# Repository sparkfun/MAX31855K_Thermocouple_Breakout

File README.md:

MAX31855K Thermocouple Breakout
========================================

[*SEN-13266*](https://www.sparkfun.com/products/13266)

The [MAX31855K](http://datasheets.maximintegrated.com/en/ds/MAX31855.pdf) IC takes a standard k-type thermocouple in one end, digitizes the temperature measured and sends that data out the other end via [SPI](http://en.wikipedia.org/wiki/Serial_Peripheral_Interface_Bus).

This part was created in Eagle v7.2.0.

Repository Contents
-------------------

* **/Hardware** - All Eagle design files (.brd, .sch)
* **/Libraries** - All Arduino libraries and board examples
* **/Production** - Test bed files and production panel files
* **LICENSE.md** - The license this library is distributed under.
* **README.md** - This file!

Documentation
--------------

* **[Installing an Arduino Library Guide](https://learn.sparkfun.com/tutorials/installing-an-arduino-library)** - Basic information on how to install an Arduino library.
* **[Hookup Guide](https://learn.sparkfun.com/tutorials/max31855k-thermocouple-breakout-hookup-guide)** - Basic hookup guide for the MAX31855K Thermocouple Breakout.

Product Versions
----------------
* [*SEN-13266*](https://www.sparkfun.com/products/13266) - K-type thermocouple digitizer breakout board

Version History
---------------
* [v1.0](https://www.sparkfun.com/products/13266) MAX31855K Thermocouple Breakout

License Information
-------------------

This product is _**open source**_!

Please review the LICENSE.md file for license information.

If you have any questions or concerns on licensing, please contact techsupport@sparkfun.com.

Distributed as-is; no warranty is given.

- Your friends at SparkFun.

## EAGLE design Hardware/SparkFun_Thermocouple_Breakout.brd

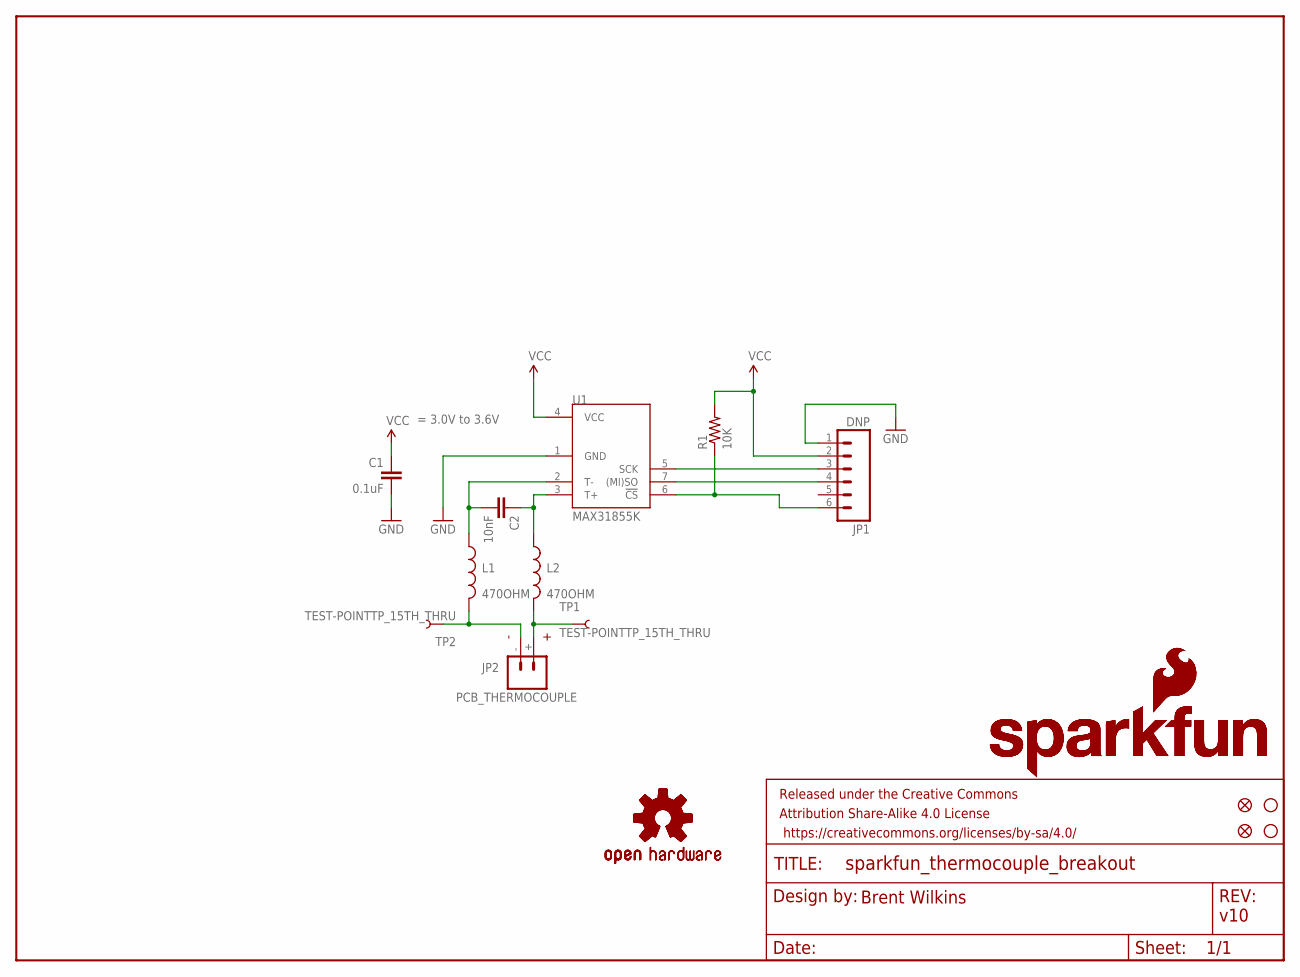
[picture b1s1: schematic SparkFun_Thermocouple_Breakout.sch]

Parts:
C1: 0.1uF; 0603-CAP
C2: 10nF; 0603-CAP
FID1, FID2: FIDUCIAL1X2; FIDUCIAL-1X2
FRAME1: >VERSION; CREATIVE_COMMONS
JP1: DNP; 1X06
JP2: PCB_THERMOCOUPLE; PCC-SMP
L1, L2: 470OHM; 0603
LOGO1, LOGO4: OSHW-LOGOS; OSHW-LOGO-S
LOGO2, LOGO3: SFE_LOGO_NAME_FLAME.1_INCH; SFE_LOGO_NAME_FLAME_.1
R1: 10K; 0603-RES
STANDOFF1, STANDOFF4: STAND-OFF
TP1, TP2: TEST-POINTTP_15TH_THRU; TP_15TH
U1: MAX31855K; SOIC8

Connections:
GND: C1.2, JP1.1, U1.1 (GND)
unnamed: JP1.3, U1.5 (SCK)
unnamed: JP1.4, U1.7 ((MI)SO)
unnamed: C2.2, L1.1, U1.2 (T-)
unnamed: JP2.+, L2.2, TP1.P$1
unnamed: JP2.-, L1.2, TP2.P$1
unnamed: C2.1, L2.1, U1.3 (T+)
unnamed: JP1.6, R1.1, U1.6 (!CS)
VCC: C1.1, JP1.2, R1.2, U1.4 (VCC)

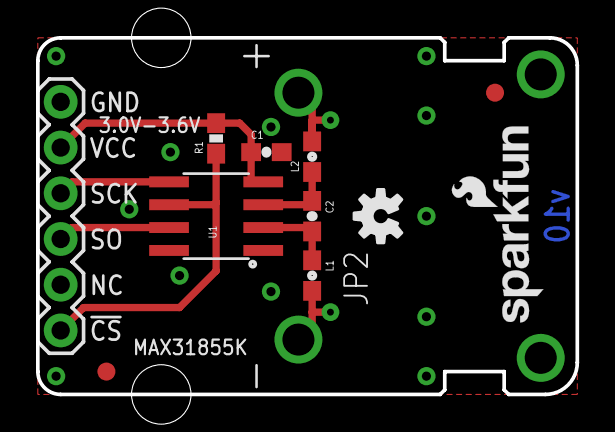
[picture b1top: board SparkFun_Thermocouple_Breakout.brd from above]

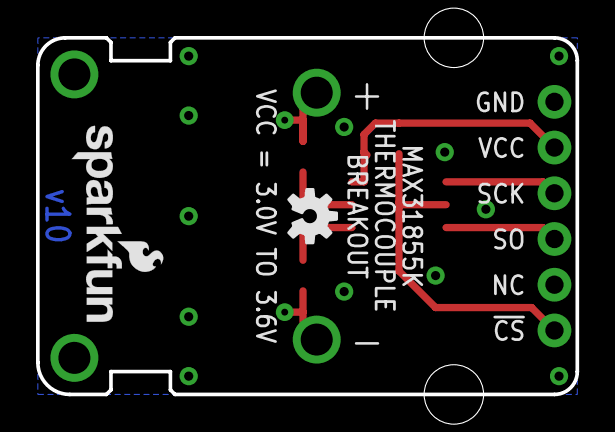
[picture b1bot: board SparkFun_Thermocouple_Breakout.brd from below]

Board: 2 copper layers, 30.0 x 19.8 mm, 19 parts (2 on the bottom side), 9 nets.

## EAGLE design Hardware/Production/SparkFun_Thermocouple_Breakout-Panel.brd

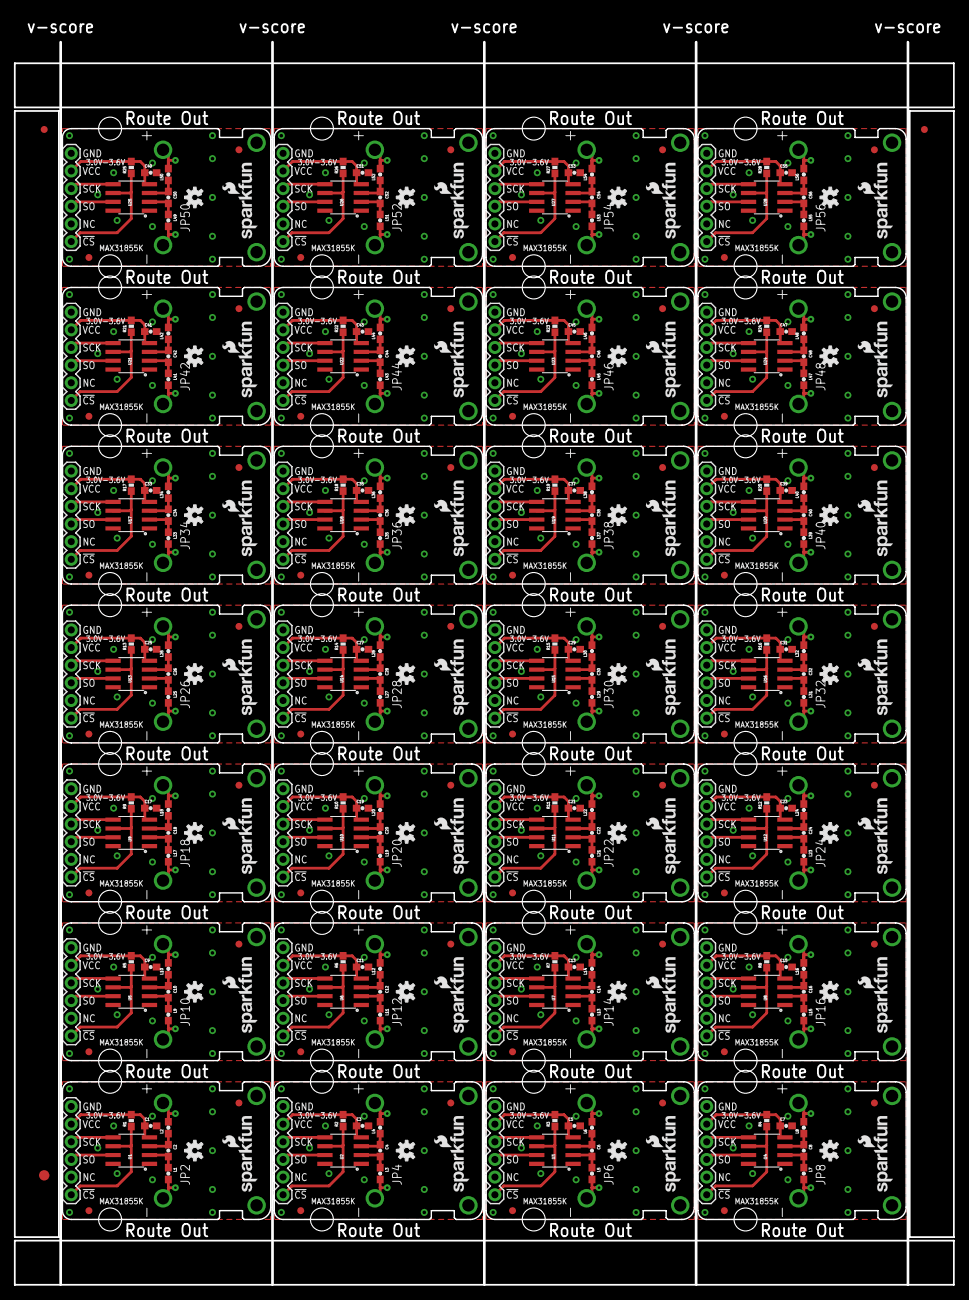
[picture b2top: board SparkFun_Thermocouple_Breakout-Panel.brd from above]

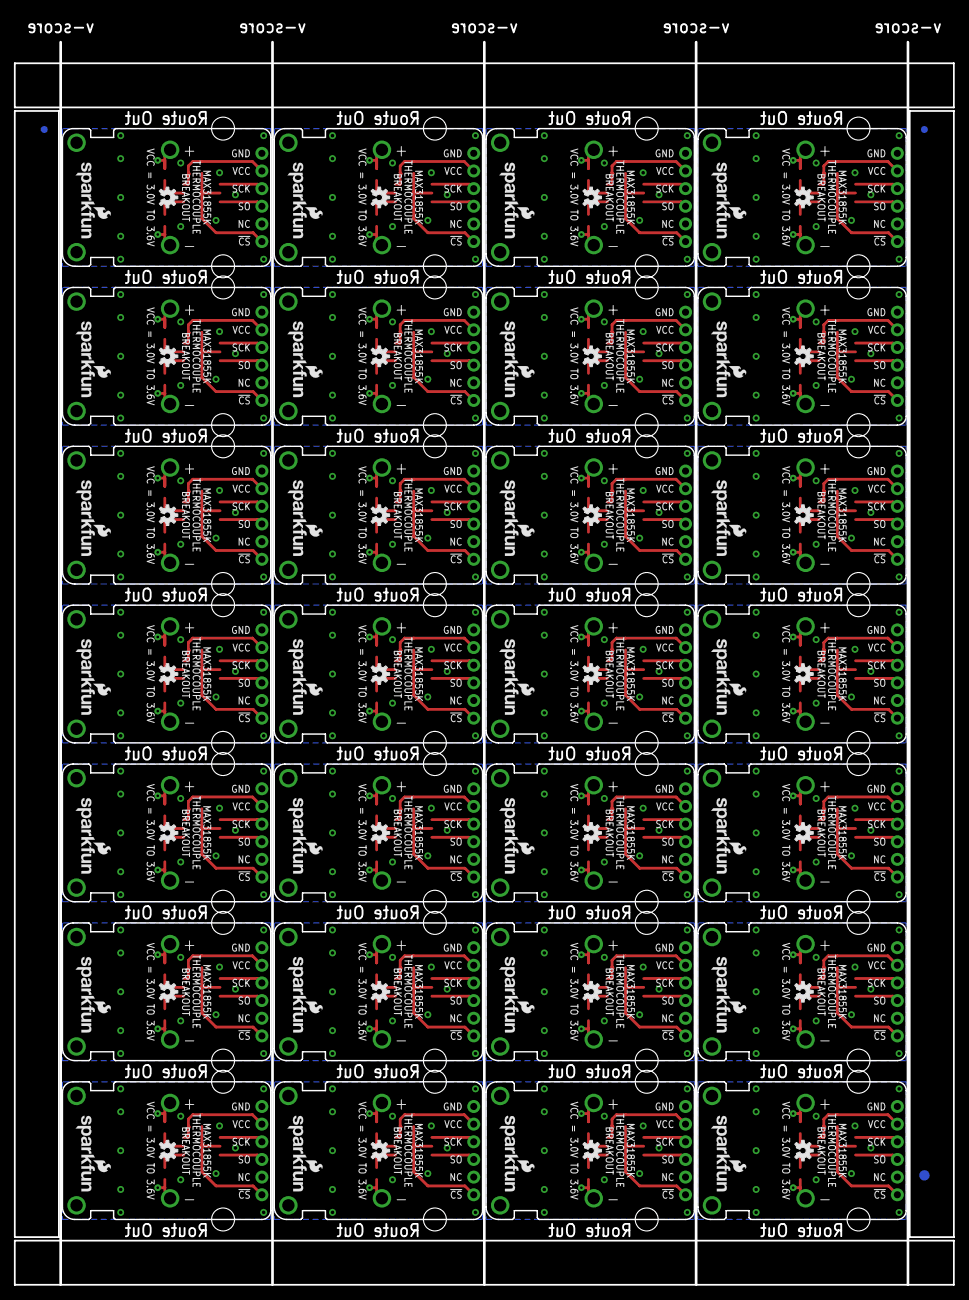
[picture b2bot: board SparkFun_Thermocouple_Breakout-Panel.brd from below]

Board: 2 copper layers, 135.0 x 182.7 mm, 510 parts (59 on the bottom side), 252 nets.

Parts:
C1, C3, C5, C7, C9, C11, C13, C15, C17, C19, C21, C23, C25, C27, C29, C31, C33, C35, C37, C39, C41, C43, C45, C47, C49, C51, C53, C55: 0.1uF; 0603-CAP
C2, C4, C6, C8, C10, C12, C14, C16, C18, C20, C22, C24, C26, C28, C30, C32, C34, C36, C38, C40, C42, C44, C46, C48, C50, C52, C54, C56: 10nF; 0603-CAP
E$1, E$2, E$3, E$4: FIDUCIAL-1X2
E$5, E$6: FIDUCIAL-1.5X3
FID1, FID2, FID3, FID4, FID5, FID6, FID7, FID8, FID9, FID10, FID11, FID12, FID13, FID14, FID15, FID16, FID17, FID18, FID19, FID20, FID21, FID22, FID23, FID24, FID25, FID26, FID27, FID28, FID29, FID30, FID31, FID32, FID33, FID34, FID35, FID36, FID37, FID38, FID39, FID40, FID41, FID42, FID43, FID44, FID45, FID46, FID47, FID48, FID49, FID50, FID51, FID52, FID53, FID54, FID55, FID56: FIDUCIAL1X2; FIDUCIAL-1X2
JP1, JP3, JP5, JP7, JP9, JP11, JP13, JP15, JP17, JP19, JP21, JP23, JP25, JP27, JP29, JP31, JP33, JP35, JP37, JP39, JP41, JP43, JP45, JP47, JP49, JP51, JP53, JP55: DNP; 1X06
JP2, JP4, JP6, JP8, JP10, JP12, JP14, JP16, JP18, JP20, JP22, JP24, JP26, JP28, JP30, JP32, JP34, JP36, JP38, JP40, JP42, JP44, JP46, JP48, JP50, JP52, JP54, JP56: PCB_THERMOCOUPLE; PCC-SMP
L1, L2, L3, L4, L5, L6, L7, L8, L9, L10, L11, L12, L13, L14, L15, L16, L17, L18, L19, L20, L21, L22, L23, L24, L25, L26, L27, L28, L29, L30, L31, L32, L33, L34, L35, L36, L37, L38, L39, L40, L41, L42, L43, L44, L45, L46, L47, L48, L49, L50, L51, L52, L53, L54, L55, L56: 470OHM; 0603
LOGO1, LOGO4, LOGO6, LOGO8, LOGO10, LOGO12, LOGO14, LOGO16, LOGO18, LOGO20, LOGO22, LOGO24, LOGO26, LOGO28, LOGO30, LOGO32, LOGO34, LOGO36, LOGO38, LOGO40, LOGO42, LOGO44, LOGO46, LOGO48, LOGO50, LOGO52, LOGO54, LOGO56, LOGO58, LOGO60, LOGO62, LOGO64, LOGO66, LOGO68, LOGO70, LOGO72, LOGO74, LOGO76, LOGO78, LOGO80, LOGO82, LOGO84, LOGO86, LOGO88, LOGO90, LOGO92, LOGO94, LOGO96, LOGO98, LOGO100, LOGO102, LOGO104, LOGO106, LOGO108, LOGO110, LOGO112: OSHW-LOGOS; OSHW-LOGO-S
LOGO2, LOGO3, LOGO5, LOGO7, LOGO9, LOGO11, LOGO13, LOGO15, LOGO17, LOGO19, LOGO21, LOGO23, LOGO25, LOGO27, LOGO29, LOGO31, LOGO33, LOGO35, LOGO37, LOGO39, LOGO41, LOGO43, LOGO45, LOGO47, LOGO49, LOGO51, LOGO53, LOGO55, LOGO57, LOGO59, LOGO61, LOGO63, LOGO65, LOGO67, LOGO69, LOGO71, LOGO73, LOGO75, LOGO77, LOGO79, LOGO81, LOGO83, LOGO85, LOGO87, LOGO89, LOGO91, LOGO93, LOGO95, LOGO97, LOGO99, LOGO101, LOGO103, LOGO105, LOGO107, LOGO109, LOGO111: SFE_LOGO_NAME_FLAME.1_INCH; SFE_LOGO_NAME_FLAME_.1
R1, R2, R3, R4, R5, R6, R7, R8, R9, R10, R11, R12, R13, R14, R15, R16, R17, R18, R19, R20, R21, R22, R23, R24, R25, R26, R27, R28: 10K; 0603-RES
STANDOFF1, STANDOFF2, STANDOFF3, STANDOFF4, STANDOFF5, STANDOFF6, STANDOFF7, STANDOFF8, STANDOFF9, STANDOFF10, STANDOFF11, STANDOFF12, STANDOFF13, STANDOFF14, STANDOFF15, STANDOFF16, STANDOFF17, STANDOFF18, STANDOFF19, STANDOFF20, STANDOFF21, STANDOFF22, STANDOFF23, STANDOFF24, STANDOFF25, STANDOFF26, STANDOFF27, STANDOFF28, STANDOFF29, STANDOFF30, STANDOFF31, STANDOFF32, STANDOFF33, STANDOFF34, STANDOFF35, STANDOFF36, STANDOFF37, STANDOFF38, STANDOFF39, STANDOFF40, STANDOFF41, STANDOFF42, STANDOFF43, STANDOFF44, STANDOFF45, STANDOFF46, STANDOFF47, STANDOFF48, STANDOFF49, STANDOFF50, STANDOFF51, STANDOFF52, STANDOFF53, STANDOFF54, STANDOFF55, STANDOFF56: STAND-OFF
TP1, TP2, TP3, TP4, TP5, TP6, TP7, TP8, TP9, TP10, TP11, TP12, TP13, TP14, TP15, TP16, TP17, TP18, TP19, TP20, TP21, TP22, TP23, TP24, TP25, TP26, TP27, TP28, TP29, TP30, TP31, TP32, TP33, TP34, TP35, TP36, TP37, TP38, TP39, TP40, TP41, TP42, TP43, TP44, TP45, TP46, TP47, TP48, TP49, TP50, TP51, TP52, TP53, TP54, TP55, TP56: TEST-POINTTP_15TH_THRU; TP_15TH
U1, U2, U3, U4, U5, U6, U7, U8, U9, U10, U11, U12, U13, U14, U15, U16, U17, U18, U19, U20, U21, U22, U23, U24, U25, U26, U27, U28: MAX31855K; SOIC8

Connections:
GND: C1.2, JP1.1, U1.1
GND1: C3.2, JP3.1, U2.1
GND2: C5.2, JP5.1, U3.1
GND3: C7.2, JP7.1, U4.1
GND4: C9.2, JP9.1, U5.1
GND5: C11.2, JP11.1, U6.1
GND6: C13.2, JP13.1, U7.1
GND7: C15.2, JP15.1, U8.1
GND8: C17.2, JP17.1, U9.1
GND9: C19.2, JP19.1, U10.1
GND10: C21.2, JP21.1, U11.1
GND11: C23.2, JP23.1, U12.1
GND12: C25.2, JP25.1, U13.1
GND13: C27.2, JP27.1, U14.1
GND14: C29.2, JP29.1, U15.1
GND15: C31.2, JP31.1, U16.1
GND16: C33.2, JP33.1, U17.1
GND17: C35.2, JP35.1, U18.1
GND18: C37.2, JP37.1, U19.1
GND19: C39.2, JP39.1, U20.1
GND20: C41.2, JP41.1, U21.1
GND21: C43.2, JP43.1, U22.1
GND22: C45.2, JP45.1, U23.1
GND23: C47.2, JP47.1, U24.1
GND24: C49.2, JP49.1, U25.1
GND25: C51.2, JP51.1, U26.1
GND26: C53.2, JP53.1, U27.1
GND27: C55.2, JP55.1, U28.1
unnamed: JP1.3, U1.5
unnamed: JP1.4, U1.7
unnamed: C2.2, L1.1, U1.2
unnamed: JP2.+, L2.2, TP1.P$1
unnamed: JP2.-, L1.2, TP2.P$1
unnamed: C4.1, L4.1, U2.3
unnamed: C2.1, L2.1, U1.3
unnamed: JP1.6, R1.1, U1.6
unnamed: JP3.3, U2.5
unnamed: JP3.4, U2.7
unnamed: JP3.6, R2.1, U2.6
unnamed: C4.2, L3.1, U2.2
unnamed: JP4.-, L3.2, TP4.P$1
unnamed: JP4.+, L4.2, TP3.P$1
unnamed: C6.1, L6.1, U3.3
unnamed: JP5.3, U3.5
unnamed: JP5.4, U3.7
unnamed: JP5.6, R3.1, U3.6
unnamed: C6.2, L5.1, U3.2
unnamed: JP6.-, L5.2, TP6.P$1
unnamed: JP6.+, L6.2, TP5.P$1
unnamed: C8.1, L8.1, U4.3
unnamed: JP7.3, U4.5
unnamed: JP7.4, U4.7
unnamed: JP7.6, R4.1, U4.6
unnamed: C8.2, L7.1, U4.2
unnamed: JP8.-, L7.2, TP8.P$1
unnamed: JP8.+, L8.2, TP7.P$1
unnamed: C10.1, L10.1, U5.3
unnamed: JP9.3, U5.5
unnamed: JP9.4, U5.7
unnamed: JP9.6, R5.1, U5.6
unnamed: C10.2, L9.1, U5.2
unnamed: JP10.-, L9.2, TP10.P$1
unnamed: JP10.+, L10.2, TP9.P$1
unnamed: C12.1, L12.1, U6.3
unnamed: JP11.3, U6.5
unnamed: JP11.4, U6.7
unnamed: JP11.6, R6.1, U6.6
unnamed: C12.2, L11.1, U6.2
unnamed: JP12.-, L11.2, TP12.P$1
unnamed: JP12.+, L12.2, TP11.P$1
unnamed: C14.1, L14.1, U7.3
unnamed: JP13.3, U7.5
unnamed: JP13.4, U7.7
unnamed: JP13.6, R7.1, U7.6
unnamed: C14.2, L13.1, U7.2
unnamed: JP14.-, L13.2, TP14.P$1
unnamed: JP14.+, L14.2, TP13.P$1
unnamed: C16.1, L16.1, U8.3
unnamed: JP15.3, U8.5
unnamed: JP15.4, U8.7
unnamed: JP15.6, R8.1, U8.6
unnamed: C16.2, L15.1, U8.2
unnamed: JP16.-, L15.2, TP16.P$1
unnamed: JP16.+, L16.2, TP15.P$1
unnamed: C18.1, L18.1, U9.3
unnamed: JP17.3, U9.5
unnamed: JP17.4, U9.7
unnamed: JP17.6, R9.1, U9.6
unnamed: C18.2, L17.1, U9.2
unnamed: JP18.-, L17.2, TP18.P$1
unnamed: JP18.+, L18.2, TP17.P$1
unnamed: C20.1, L20.1, U10.3
unnamed: JP19.3, U10.5
unnamed: JP19.4, U10.7
unnamed: JP19.6, R10.1, U10.6
unnamed: C20.2, L19.1, U10.2
unnamed: JP20.-, L19.2, TP20.P$1
unnamed: JP20.+, L20.2, TP19.P$1
unnamed: C22.1, L22.1, U11.3
unnamed: JP21.3, U11.5
unnamed: JP21.4, U11.7
unnamed: JP21.6, R11.1, U11.6
unnamed: C22.2, L21.1, U11.2
unnamed: JP22.-, L21.2, TP22.P$1
unnamed: JP22.+, L22.2, TP21.P$1
unnamed: C24.1, L24.1, U12.3
unnamed: JP23.3, U12.5
unnamed: JP23.4, U12.7
unnamed: JP23.6, R12.1, U12.6
unnamed: C24.2, L23.1, U12.2
unnamed: JP24.-, L23.2, TP24.P$1
unnamed: JP24.+, L24.2, TP23.P$1
unnamed: C26.1, L26.1, U13.3
unnamed: JP25.3, U13.5
unnamed: JP25.4, U13.7
unnamed: JP25.6, R13.1, U13.6
unnamed: C26.2, L25.1, U13.2
unnamed: JP26.-, L25.2, TP26.P$1
unnamed: JP26.+, L26.2, TP25.P$1
unnamed: C28.1, L28.1, U14.3
unnamed: JP27.3, U14.5
unnamed: JP27.4, U14.7
unnamed: JP27.6, R14.1, U14.6
unnamed: C28.2, L27.1, U14.2
unnamed: JP28.-, L27.2, TP28.P$1
unnamed: JP28.+, L28.2, TP27.P$1
unnamed: C30.1, L30.1, U15.3
unnamed: JP29.3, U15.5
unnamed: JP29.4, U15.7
unnamed: JP29.6, R15.1, U15.6
unnamed: C30.2, L29.1, U15.2
unnamed: JP30.-, L29.2, TP30.P$1
unnamed: JP30.+, L30.2, TP29.P$1
unnamed: C32.1, L32.1, U16.3
unnamed: JP31.3, U16.5
unnamed: JP31.4, U16.7
unnamed: JP31.6, R16.1, U16.6
unnamed: C32.2, L31.1, U16.2
unnamed: JP32.-, L31.2, TP32.P$1
unnamed: JP32.+, L32.2, TP31.P$1
unnamed: C34.1, L34.1, U17.3
unnamed: JP33.3, U17.5
unnamed: JP33.4, U17.7
unnamed: JP33.6, R17.1, U17.6
unnamed: C34.2, L33.1, U17.2
unnamed: JP34.-, L33.2, TP34.P$1
unnamed: JP34.+, L34.2, TP33.P$1
unnamed: C36.1, L36.1, U18.3
unnamed: JP35.3, U18.5
unnamed: JP35.4, U18.7
unnamed: JP35.6, R18.1, U18.6
unnamed: C36.2, L35.1, U18.2
unnamed: JP36.-, L35.2, TP36.P$1
unnamed: JP36.+, L36.2, TP35.P$1
unnamed: C38.1, L38.1, U19.3
unnamed: JP37.3, U19.5
unnamed: JP37.4, U19.7
unnamed: JP37.6, R19.1, U19.6
unnamed: C38.2, L37.1, U19.2
unnamed: JP38.-, L37.2, TP38.P$1
unnamed: JP38.+, L38.2, TP37.P$1
unnamed: C40.1, L40.1, U20.3
unnamed: JP39.3, U20.5
unnamed: JP39.4, U20.7
unnamed: JP39.6, R20.1, U20.6
unnamed: C40.2, L39.1, U20.2
unnamed: JP40.-, L39.2, TP40.P$1
unnamed: JP40.+, L40.2, TP39.P$1
unnamed: C42.1, L42.1, U21.3
unnamed: JP41.3, U21.5
unnamed: JP41.4, U21.7
unnamed: JP41.6, R21.1, U21.6
unnamed: C42.2, L41.1, U21.2
unnamed: JP42.-, L41.2, TP42.P$1
unnamed: JP42.+, L42.2, TP41.P$1
unnamed: C44.1, L44.1, U22.3
unnamed: JP43.3, U22.5
unnamed: JP43.4, U22.7
unnamed: JP43.6, R22.1, U22.6
unnamed: C44.2, L43.1, U22.2
unnamed: JP44.-, L43.2, TP44.P$1
unnamed: JP44.+, L44.2, TP43.P$1
unnamed: C46.1, L46.1, U23.3
unnamed: JP45.3, U23.5
unnamed: JP45.4, U23.7
unnamed: JP45.6, R23.1, U23.6
unnamed: C46.2, L45.1, U23.2
unnamed: JP46.-, L45.2, TP46.P$1
unnamed: JP46.+, L46.2, TP45.P$1
unnamed: C48.1, L48.1, U24.3
unnamed: JP47.3, U24.5
unnamed: JP47.4, U24.7
unnamed: JP47.6, R24.1, U24.6
unnamed: C48.2, L47.1, U24.2
unnamed: JP48.-, L47.2, TP48.P$1
unnamed: JP48.+, L48.2, TP47.P$1
unnamed: C50.1, L50.1, U25.3
unnamed: JP49.3, U25.5
unnamed: JP49.4, U25.7
unnamed: JP49.6, R25.1, U25.6
unnamed: C50.2, L49.1, U25.2
unnamed: JP50.-, L49.2, TP50.P$1
unnamed: JP50.+, L50.2, TP49.P$1
unnamed: C52.1, L52.1, U26.3
unnamed: JP51.3, U26.5
unnamed: JP51.4, U26.7
unnamed: JP51.6, R26.1, U26.6
unnamed: C52.2, L51.1, U26.2
unnamed: JP52.-, L51.2, TP52.P$1
unnamed: JP52.+, L52.2, TP51.P$1
unnamed: C54.1, L54.1, U27.3
unnamed: JP53.3, U27.5
unnamed: JP53.4, U27.7
unnamed: JP53.6, R27.1, U27.6
unnamed: C54.2, L53.1, U27.2
unnamed: JP54.-, L53.2, TP54.P$1
unnamed: JP54.+, L54.2, TP53.P$1
unnamed: C56.1, L56.1, U28.3
unnamed: JP55.3, U28.5
unnamed: JP55.4, U28.7
unnamed: JP55.6, R28.1, U28.6
unnamed: C56.2, L55.1, U28.2
unnamed: JP56.-, L55.2, TP56.P$1
unnamed: JP56.+, L56.2, TP55.P$1
VCC: C1.1, JP1.2, R1.2, U1.4
VCC1: C3.1, JP3.2, R2.2, U2.4
VCC2: C5.1, JP5.2, R3.2, U3.4
VCC3: C7.1, JP7.2, R4.2, U4.4
VCC4: C9.1, JP9.2, R5.2, U5.4
VCC5: C11.1, JP11.2, R6.2, U6.4
VCC6: C13.1, JP13.2, R7.2, U7.4
VCC7: C15.1, JP15.2, R8.2, U8.4
VCC8: C17.1, JP17.2, R9.2, U9.4
VCC9: C19.1, JP19.2, R10.2, U10.4
VCC10: C21.1, JP21.2, R11.2, U11.4
VCC11: C23.1, JP23.2, R12.2, U12.4
VCC12: C25.1, JP25.2, R13.2, U13.4
VCC13: C27.1, JP27.2, R14.2, U14.4
VCC14: C29.1, JP29.2, R15.2, U15.4
VCC15: C31.1, JP31.2, R16.2, U16.4
VCC16: C33.1, JP33.2, R17.2, U17.4
VCC17: C35.1, JP35.2, R18.2, U18.4
VCC18: C37.1, JP37.2, R19.2, U19.4
VCC19: C39.1, JP39.2, R20.2, U20.4
VCC20: C41.1, JP41.2, R21.2, U21.4
VCC21: C43.1, JP43.2, R22.2, U22.4
VCC22: C45.1, JP45.2, R23.2, U23.4
VCC23: C47.1, JP47.2, R24.2, U24.4
VCC24: C49.1, JP49.2, R25.2, U25.4
VCC25: C51.1, JP51.2, R26.2, U26.4
VCC26: C53.1, JP53.2, R27.2, U27.4
VCC27: C55.1, JP55.2, R28.2, U28.4

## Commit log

2015-03-31 Did schematic capture, layout, and got some code ready to test.
2015-03-31 Removed acid trap and nudged a via
2015-03-31 Added a second logo to the back, mirrored the revision, & added the version number to the frame that disappeared with the new version of the frame
2015-03-31 Added more logos!
2015-04-01 Fixed acid trap on main IC VCC pin
2015-04-02 Added testpoints for the thermocouple connections
2015-04-30 Changed version to v10
2015-04-30 Approved restrict errors for issue #3
2015-04-30 Decreased dimension width by 0.002 inches for issue #3
2015-05-01 Swapped a pin
2015-05-04 slid a via over
2015-05-06 created panel v10
2015-06-10 Added attributes and license files
2015-06-11 updates to README
2015-06-11 Hopefully finished README
2015-06-12 Started Fritzing part
2015-06-16 finished Fritzing diagram
2015-06-19 Removed Fritzing
2015-06-19 Squashed 'Libraries/Arduino/' content from commit 9d8854e
    git-subtree-dir: Libraries/Arduino
    git-subtree-split: 9d8854e0b77ef2fbc0bcfaa76da3a5a115c86432
2015-06-19 Added Libraries/README.md
2021-10-29 Update gerbers with GKO layer.
2021-11-15 Repanelize for route outs.

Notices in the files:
parts and their libraries:
SparkFun-Aesthetics: Licensing: CC v3.0 Share-Alike You are welcome to use this library for commercial purposes.
SparkFun-AnalogIC: Licensing:Creative Commons ShareAlike 4.0 International - https://creativecommons.org/licenses/by-sa/4.0
SparkFun-Aesthetics: Released under the Creative Commons
